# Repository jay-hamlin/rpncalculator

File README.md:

# rpncalculator
RPN Calculator inspired by the HP-97

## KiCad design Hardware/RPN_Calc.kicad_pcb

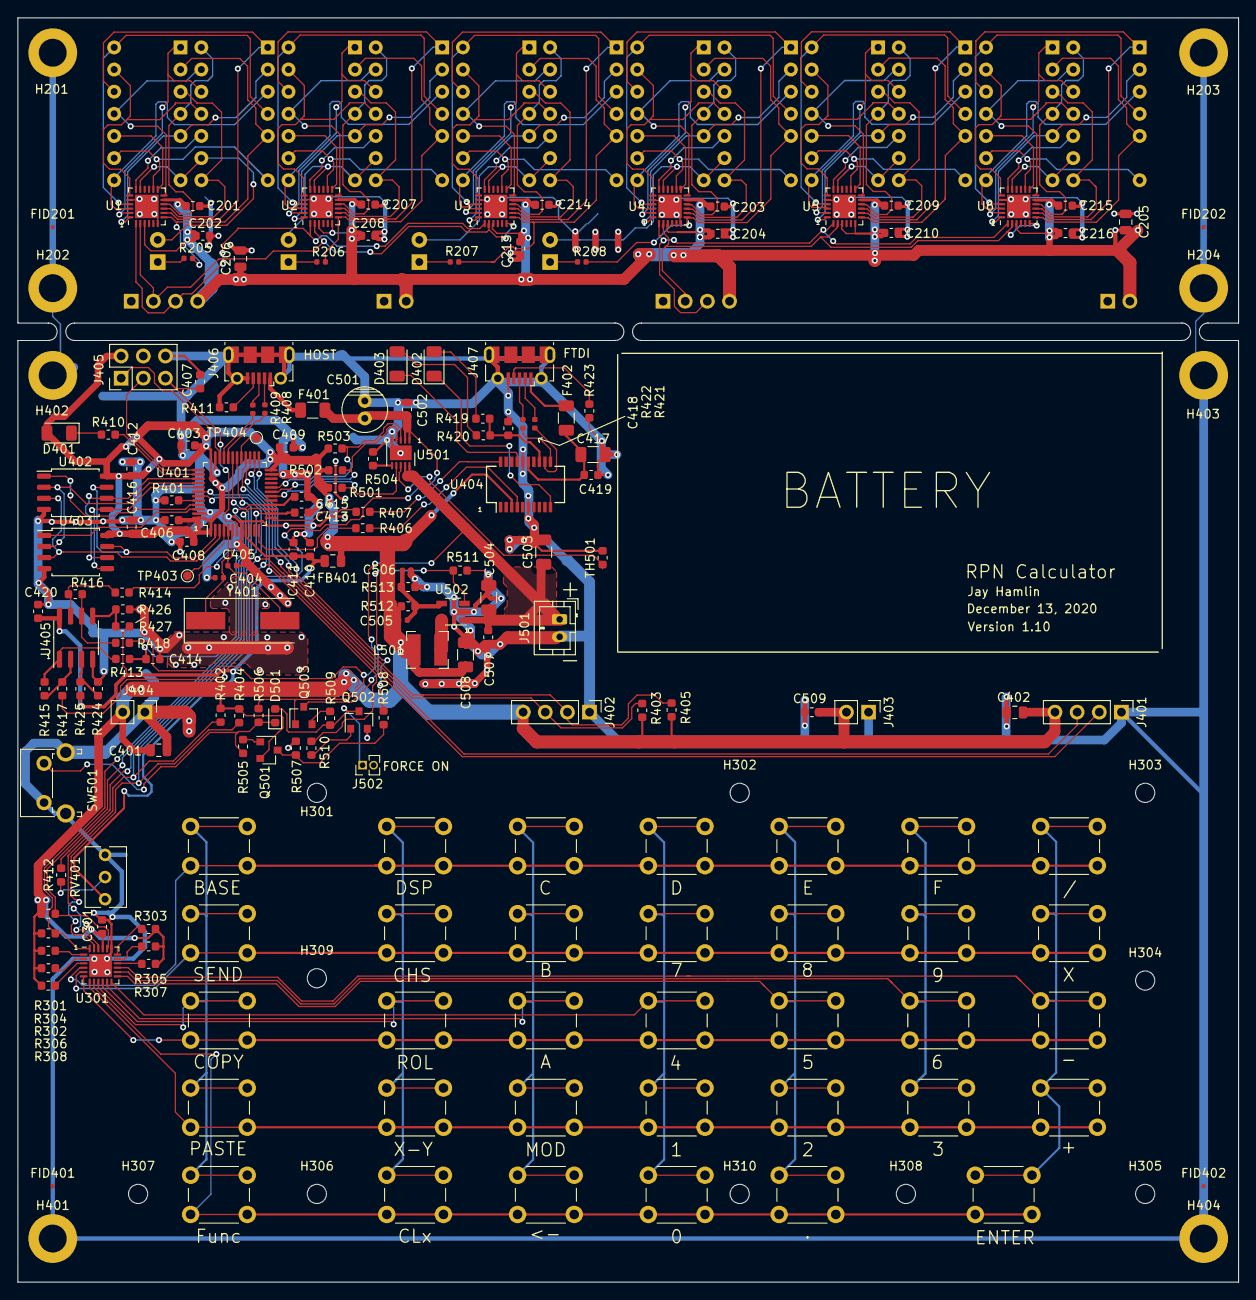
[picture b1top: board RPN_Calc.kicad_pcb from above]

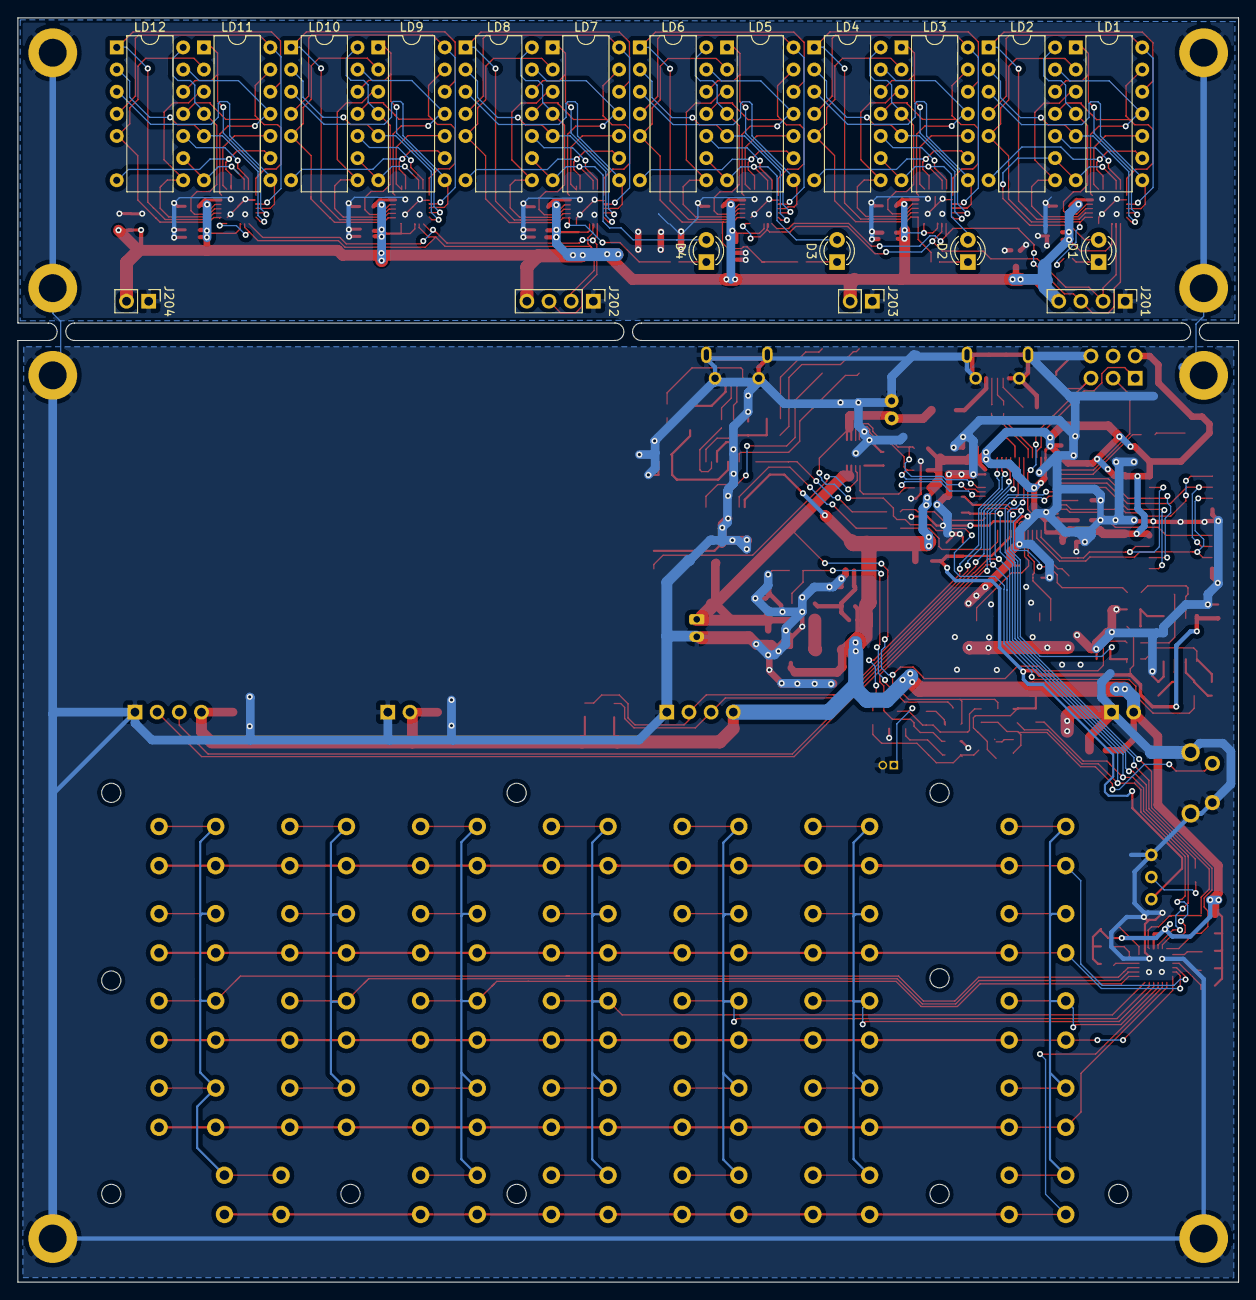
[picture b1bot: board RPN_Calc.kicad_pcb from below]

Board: 2 copper layers, 140.0 x 145.0 mm, 212 parts (20 on the bottom side), 186 nets.

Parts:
0, 1, 2, 3, 4, 5, 6, 7, 8, 9, .: TL1105SPF; SW_PUSH_TL1105
+: TL1105SPF; SW_PUSH_TL1105
-: TL1105SPF; SW_PUSH_TL1105
/: TL1105SPF; SW_PUSH_TL1105
<-: TL1105SPF; SW_PUSH_TL1105
A: TL1105SPF; SW_PUSH_TL1105
B: TL1105SPF; SW_PUSH_TL1105
BASE: TL1105SPF; SW_PUSH_TL1105
C: TL1105SPF; SW_PUSH_TL1105
C201, C203, C207, C209, C213, C215, C301, C403, C406, C407, C408, C409, C410, C412, C413, C414, C415, C416, C418, C419, C420, C507, C509: 100nF; C_0603_1608Metric
C202, C204, C208, C210, C214, C216, C411, C502: 1uF; C_0603_1608Metric
C205, C206, C401, C402: 4.7uF; C_0805_2012Metric
C404, C405: 20pF; C_0402_1005Metric
C417, C503, C504, C508: 10uF; C_1206_3216Metric
C501: 33uF; C_Radial_D5.0mm_H11.0mm_P2.00mm
C505: 7.0pF; C_0402_1005Metric
C506: 33pF; C_0402_1005Metric
CHS: TL1105SPF; SW_PUSH_TL1105
CLx: TL1105SPF; SW_PUSH_TL1105
COPY: TL1105SPF; SW_PUSH_TL1105
D: TL1105SPF; SW_PUSH_TL1105
D1, D2, D3, D4: LED; LED_D3.0mm
D401: LED_GREEN; LED_1206_3216Metric
D402, D403: LED; LED_1206_3216Metric
D501: CDBU0240; D_0603_1608Metric
DSP: TL1105SPF; SW_PUSH_TL1105
E: TL1105SPF; SW_PUSH_TL1105
ENTER: TL1105SPF; SW_PUSH_TL1105
F: TL1105SPF; SW_PUSH_TL1105
F401, F402: Polyfuse_Small; Fuse_1206_3216Metric
FB401: Ferrite_Bead_Small; L_0805_2012Metric
FID201, FID202, FID401, FID402: Fiducial; Fiducial_0.5mm_Mask1mm
Func: TL1105SPF; SW_PUSH_TL1105
H201, H202, H203, H204, H401, H402, H403, H404: MountingHole_Pad; MountingHole_3.2mm_M3_DIN965_Pad
H301, H302, H303, H304, H305, H306, H307, H308, H309, H310: MountingHole; MountingHole_2.2mm_M2
J201, J202, J401, J402: Conn_01x04; PinHeader_1x04_P2.54mm_Vertical
J203, J204, J403, J404: Conn_01x02; PinHeader_1x02_P2.54mm_Vertical
J405: Conn_02x03_Odd_Even; PinHeader_2x03_P2.54mm_Vertical
J406, J407: USB_B_Micro; USB_Micro-B_Molex-105017-0001
J501: JST PTH 2.0mm vertical; JST_PH_B2B-PH-K_1x02_P2.00mm_Vertical
J502: HDR_1x2_50mil; PinHeader_1x02_P1.27mm_Vertical
L501: 2.2uH; L_Bourns-SRN4018
LD1, LD2, LD3, LD4, LD5, LD6, LD7, LD8, LD9, LD10, LD11, LD12: LTP-305HR; DIP-14_LTP-305HR
MOD: TL1105SPF; SW_PUSH_TL1105
PASTE: TL1105SPF; SW_PUSH_TL1105
Q501, Q503: MMBT3906; SOT-23
Q502: 2N7002; SOT-23
R205, R206, R207, R208, R408, R409, R421, R422: 20R; R_0402_1005Metric
R301, R302, R303, R304, R305, R306, R307, R308, R411, R423, R501, R502, R503, R505, R506, R507, R509, R511: 100K; R_0603_1608Metric
R401: 10K; R_0603_1608Metric
R402, R403, R404, R405: 2.2K; R_0603_1608Metric
R406, R407, R412, R413, R414, R419, R420, R508, R510: 1K; R_0603_1608Metric
R410: 240R; R_0603_1608Metric
R415: 549K,1%; R_0603_1608Metric
R416, R418: 2.00M,1%; R_0603_1608Metric
R417: 1.00M,1%; R_0603_1608Metric
R424, R426: 604K,1%; R_0603_1608Metric
R425, R513: 100K,1%; R_0603_1608Metric
R427: 200K,1%; R_0603_1608Metric
R504: 7.8K,1%; R_0603_1608Metric
R512: 500K,1%; R_0603_1608Metric
ROL: TL1105SPF; SW_PUSH_TL1105
RV401: 50K, linear; Potentiometer_Bourns_3266Y_Vertical
SEND: TL1105SPF; SW_PUSH_TL1105
SW501: 1-1825027-1; SW_Tactile_SPST_Angled_PTS645Vx58-2LFS
TH501: 10K, NTC; R_0603_1608Metric
TP403: TEST3; TestPoint_Pad_D1.0mm
TP404: MCO; TestPoint_Pad_D1.0mm
U1, U2, U3, U4, U5, U6: IS31FL3730-QFN24; QFN-24-1EP_4x4mm_P0.5mm_EP2.7x2.7mm
U301: TCA8418RTWR; WQFN-24-1EP_4x4mm_P0.5mm_EP2.6x2.6mm
U401: STM32F070CBTx; LQFP-48_7x7mm_P0.5mm
U402, U403: W25Q128JVS; SOIC-8_5.23x5.23mm_P1.27mm
U404: FT231XS; SSOP-20_3.9x8.7mm_P0.635mm
U405: MCP6422T-E/SN; SOIC-8_3.9x4.9mm_P1.27mm
U501: MCP73833T-FCI_MF; DFN-10-1EP_3x3mm_P0.5mm_EP1.7x2.5mm
U502: LM3671MF; TSOT-23-5
X: TL1105SPF; SW_PUSH_TL1105
X-Y: TL1105SPF; SW_PUSH_TL1105
Y401: 8MHz(12pF); Crystal_SMD_HC49-SD

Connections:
+3V3: C201.1, C202.1, C203.1, C204.1, C205.1, C206.1, C207.1, C208.1, C209.1, C210.1, C213.1, C214.1, C215.1, C216.1, C301.1, C401.1, C402.1, C403.1, C406.1, C408.1, C409.1, C412.1, C416.1, C505.1, C508.1, C509.1, D401.2, FB401.1, J201.4, J202.4, J203.2, J204.2, J401.4, J402.4, J403.2, J404.2, J405.2, L501.2, Q501.2, R301.2, R302.2, R303.1, R304.1, R305.1, R306.1, R307.1, R308.1, R402.2, R403.2, R404.2, R405.2, R501.2, R502.2, R503.2, R512.2, U1.3, U1.11, U2.3, U2.6, U2.11, U3.3, U3.11, U4.3, U4.11, U5.3, U5.6, U5.11, U6.3, U6.11, U301.21, U401.1, U401.24, U401.36, U401.48, U402.8, U403.8, U404.3
/Sheet5F92F4CC/ADC4: C413.1, R412.2, U401.14
/Sheet5F92F4CC/ADC5: C414.1, R413.2, U401.15
/Sheet5F92F4CC/ADC6: C415.1, R414.2, U401.16
/Sheet5F92F4CC/EM1_CS: U401.45, U402.1
/Sheet5F92F4CC/EM2_CS: U401.46, U403.1
/Sheet5F92F4CC/EM_HOLD: U401.2, U402.7, U403.7
/Sheet5F92F4CC/EM_WP: U401.3, U402.3, U403.3
/Sheet5F92F4CC/FT3V3: C418.1, R419.2, R420.2, U404.13
/Sheet5F92F4CC/FT_USBVCC: C417.1, C419.1, F402.1, U404.15
/Sheet5F92F4CC/I2C2_SCL: J402.2, R405.1, U401.26
/Sheet5F92F4CC/I2C2_SDA: J402.3, R403.1, U401.27
/Sheet5F92F4CC/LED1: R410.2, U401.38
/Sheet5F92F4CC/MCU_RX: R407.2, U401.13
/Sheet5F92F4CC/MCU_TX: R406.2, U401.12
/Sheet5F92F4CC/NRST: C407.1, J405.5, U401.7
/Sheet5F92F4CC/OSC_IN: C404.1, U401.5, Y401.1
/Sheet5F92F4CC/OSC_OUT: C405.1, U401.6, Y401.2
/Sheet5F92F4CC/RXD: R406.1, U404.4
/Sheet5F92F4CC/SPI_MISO: U401.40, U402.2, U403.2
/Sheet5F92F4CC/SPI_MOSI: U401.41, U402.5, U403.5
/Sheet5F92F4CC/SPI_SCK: U401.39, U402.6, U403.6
/Sheet5F92F4CC/SWCLK: J405.3, U401.37
/Sheet5F92F4CC/SWDIO: J405.1, U401.34
/Sheet5F92F4CC/TXD: R407.1, U404.20
/Sheet5F92F4CC/USB_DM: R408.2, U401.32
/Sheet5F92F4CC/USB_DP: R409.2, U401.33
/Sheet5F92F4CC/VDDA: C410.1, C411.1, C420.1, FB401.2, R425.1, R427.1, RV401.3, U401.9, U405.8
/Sheet5F92F4CC/VPOT: R412.1, RV401.2
/Sheet5F938EEE/3V3_ENABLE: Q503.3, R511.2, U502.3
/Sheet5F938EEE/THERM: TH501.1, U501.8
/Sheet5FA23E6E/C1A: LD1.5, LD2.2, U1.24
/Sheet5FA23E6E/C1B: LD3.5, LD4.2, U2.24
/Sheet5FA23E6E/C1C: LD5.5, LD6.2, U3.24
/Sheet5FA23E6E/C1D: LD7.5, LD8.2, U4.24
/Sheet5FA23E6E/C1E: LD9.5, LD10.2, U5.24
/Sheet5FA23E6E/C1F: LD11.5, LD12.2, U6.24
/Sheet5FA23E6E/C2A: LD1.1, LD2.12, U1.23
/Sheet5FA23E6E/C2B: LD3.1, LD4.12, U2.23
/Sheet5FA23E6E/C2C: LD5.1, LD6.12, U3.23
/Sheet5FA23E6E/C2D: LD7.1, LD8.12, U4.23
/Sheet5FA23E6E/C2E: LD9.1, LD10.12, U5.23
/Sheet5FA23E6E/C2F: LD11.1, LD12.12, U6.23
/Sheet5FA23E6E/C3A: LD1.8, LD2.3, U1.22
/Sheet5FA23E6E/C3B: LD3.8, LD4.3, U2.22
/Sheet5FA23E6E/C3C: LD5.8, LD6.3, U3.22
/Sheet5FA23E6E/C3D: LD7.8, LD8.3, U4.22
/Sheet5FA23E6E/C3E: LD9.8, LD10.3, U5.22
/Sheet5FA23E6E/C3F: LD11.8, LD12.3, U6.22
/Sheet5FA23E6E/C4A: LD1.14, LD2.4, U1.21
/Sheet5FA23E6E/C4B: LD3.14, LD4.4, U2.21
/Sheet5FA23E6E/C4C: LD5.14, LD6.4, U3.21
/Sheet5FA23E6E/C4D: LD7.14, LD8.4, U4.21
/Sheet5FA23E6E/C4E: LD9.14, LD10.4, U5.21
/Sheet5FA23E6E/C4F: LD11.14, LD12.4, U6.21
/Sheet5FA23E6E/C5A: LD1.13, LD2.11, U1.19
/Sheet5FA23E6E/C5B: LD3.13, LD4.11, U2.19
/Sheet5FA23E6E/C5C: LD5.13, LD6.11, U3.19
/Sheet5FA23E6E/C5D: LD7.13, LD8.11, U4.19
/Sheet5FA23E6E/C5E: LD9.13, LD10.11, U5.19
/Sheet5FA23E6E/C5F: LD11.13, LD12.11, U6.19
/Sheet5FA23E6E/C6A: LD2.10, U1.18
/Sheet5FA23E6E/C6B: LD4.10, U2.18
/Sheet5FA23E6E/C6C: LD6.10, U3.18
/Sheet5FA23E6E/C6D: LD8.10, U4.18
/Sheet5FA23E6E/C6E: LD10.10, U5.18
/Sheet5FA23E6E/C6F: LD12.10, U6.18
/Sheet5FA23E6E/C7A: D1.2, LD1.7, LD2.9, U1.17
/Sheet5FA23E6E/C7B: D2.2, LD3.7, LD4.9, U2.17
/Sheet5FA23E6E/C7C: D3.2, LD5.7, LD6.9, U3.17
/Sheet5FA23E6E/C7D: D4.2, LD7.7, LD8.9, U4.17
/Sheet5FA23E6E/C7E: LD9.7, LD10.9, U5.17
/Sheet5FA23E6E/C7F: LD11.7, LD12.9, U6.17
/Sheet5FA23E6E/R1A: LD1.2, LD2.5, R205.2, U1.7
/Sheet5FA23E6E/R1B: LD3.2, LD4.5, R206.2, U2.7
/Sheet5FA23E6E/R1C: LD5.2, LD6.5, R207.2, U3.7
/Sheet5FA23E6E/R1D: LD7.2, LD8.5, R208.2, U4.7
/Sheet5FA23E6E/R1E: LD9.2, LD10.5, U5.7
/Sheet5FA23E6E/R1F: LD11.2, LD12.5, U6.7
/Sheet5FA23E6E/R2A: LD1.12, LD2.1, U1.8
/Sheet5FA23E6E/R2B: LD3.12, LD4.1, U2.8
/Sheet5FA23E6E/R2C: LD5.12, LD6.1, U3.8
/Sheet5FA23E6E/R2D: LD7.12, LD8.1, U4.8
/Sheet5FA23E6E/R2E: LD9.12, LD10.1, U5.8
/Sheet5FA23E6E/R2F: LD11.12, LD12.1, U6.8
/Sheet5FA23E6E/R3A: LD1.3, LD2.8, U1.9
/Sheet5FA23E6E/R3B: LD3.3, LD4.8, U2.9
/Sheet5FA23E6E/R3C: LD5.3, LD6.8, U3.9
/Sheet5FA23E6E/R3D: LD7.3, LD8.8, U4.9
/Sheet5FA23E6E/R3E: LD9.3, LD10.8, U5.9
/Sheet5FA23E6E/R3F: LD11.3, LD12.8, U6.9
/Sheet5FA23E6E/R4A: LD1.4, LD2.14, U1.10
/Sheet5FA23E6E/R4B: LD3.4, LD4.14, U2.10
/Sheet5FA23E6E/R4C: LD5.4, LD6.14, U3.10
/Sheet5FA23E6E/R4D: LD7.4, LD8.14, U4.10
/Sheet5FA23E6E/R4E: LD9.4, LD10.14, U5.10
/Sheet5FA23E6E/R4F: LD11.4, LD12.14, U6.10
/Sheet5FA23E6E/R5A: LD1.11, LD2.13, U1.12
/Sheet5FA23E6E/R5B: LD3.11, LD4.13, U2.12
/Sheet5FA23E6E/R5C: LD5.11, LD6.13, U3.12
/Sheet5FA23E6E/R5D: LD7.11, LD8.13, U4.12
/Sheet5FA23E6E/R5E: LD9.11, LD10.13, U5.12
/Sheet5FA23E6E/R5F: LD11.11, LD12.13, U6.12
/Sheet5FA23E6E/R6A: LD1.10, U1.13
/Sheet5FA23E6E/R6B: LD3.10, U2.13
/Sheet5FA23E6E/R6C: LD5.10, U3.13
/Sheet5FA23E6E/R6D: LD7.10, U4.13
/Sheet5FA23E6E/R6E: LD9.10, U5.13
/Sheet5FA23E6E/R6F: LD11.10, U6.13
/Sheet5FA23E6E/R7A: LD1.9, LD2.7, U1.14
/Sheet5FA23E6E/R7B: LD3.9, LD4.7, U2.14
/Sheet5FA23E6E/R7C: LD5.9, LD6.7, U3.14
/Sheet5FA23E6E/R7D: LD7.9, LD8.7, U4.14
/Sheet5FA23E6E/R7E: LD9.9, LD10.7, U5.14
/Sheet5FA23E6E/R7F: LD11.9, LD12.7, U6.14
/Sheet5FA23F01/SWROW0: 0.1, 0.2, ..1, ..2, <-.1, <-.2, CLx.1, CLx.2, ENTER.1, ENTER.2, Func.1, Func.2, U301.8
/Sheet5FA23F01/SW_COL0: BASE.3, BASE.4, COPY.3, COPY.4, Func.3, Func.4, PASTE.3, PASTE.4, SEND.3, SEND.4, U301.9
/Sheet5FA23F01/SW_COL1: CHS.3, CHS.4, CLx.3, CLx.4, DSP.3, DSP.4, ROL.3, ROL.4, U301.10, X-Y.3, X-Y.4
/Sheet5FA23F01/SW_COL2: <-.3, <-.4, A.3, A.4, B.3, B.4, C.3, C.4, MOD.3, MOD.4, U301.11
/Sheet5FA23F01/SW_COL3: 0.3, 0.4, 1.3, 1.4, 4.3, 4.4, 7.3, 7.4, D.3, D.4, U301.12
/Sheet5FA23F01/SW_COL4: 2.3, 2.4, 5.3, 5.4, 8.3, 8.4, ..3, ..4, E.3, E.4, U301.13
/Sheet5FA23F01/SW_COL5: 3.3, 3.4, 6.3, 6.4, 9.3, 9.4, F.3, F.4, U301.14
/Sheet5FA23F01/SW_COL6: +.3, +.4, -.3, -.4, /.3, /.4, ENTER.3, ENTER.4, U301.15, X.3, X.4
/Sheet5FA23F01/SW_ROW1: 1.1, 1.2, 2.1, 2.2, 3.1, 3.2, +.1, +.2, MOD.1, MOD.2, PASTE.1, PASTE.2, U301.7, X-Y.1, X-Y.2
/Sheet5FA23F01/SW_ROW2: 4.1, 4.2, 5.1, 5.2, 6.1, 6.2, -.1, -.2, A.1, A.2, COPY.1, COPY.2, ROL.1, ROL.2, U301.6
/Sheet5FA23F01/SW_ROW3: 7.1, 7.2, 8.1, 8.2, 9.1, 9.2, B.1, B.2, CHS.1, CHS.2, SEND.1, SEND.2, U301.5, X.1, X.2
/Sheet5FA23F01/SW_ROW4: /.1, /.2, BASE.1, BASE.2, C.1, C.2, D.1, D.2, DSP.1, DSP.2, E.1, E.2, F.1, F.2, U301.4
BATT_PG: R501.1, U401.18, U501.7
BATT_STAT1: R503.1, U401.20, U501.3
BATT_STAT2: R502.1, U401.19, U501.4
BUTTON_DN: R508.2, U401.25
GND: C201.2, C202.2, C203.2, C204.2, C205.2, C206.2, C207.2, C208.2, C209.2, C210.2, C213.2, C214.2, C215.2, C216.2, C301.2, C401.2, C402.2, C403.2, C404.2, C405.2, C406.2, C407.2, C408.2, C409.2, C410.2, C411.2, C412.2, C413.2, C414.2, C415.2, C416.2, C417.2, C418.2, C419.2, C420.2, C501.2, C502.2, C503.2, C504.2, C506.2, C507.2, C508.2, C509.2, H201.1, H202.1, H203.1, H204.1, H401.1, H402.1, H403.1, H404.1, J201.1, J202.1, J203.1, J204.1, J401.1, J402.1, J403.1, J404.1, J405.6, J406.5, J406.6, J407.5, J407.6, J501.2, J502.2, Q502.2, R401.2, R411.2, R423.2, R424.2, R426.2, R504.1, R507.1, R511.1, R513.1, RV401.1, SW501.1, SW501.3, SW501.4, TH501.2, U1.6, U1.20, U1.25, U2.20, U2.25, U3.20, U3.25, U4.6, U4.20, U4.25, U5.20, U5.25, U6.20, U6.25, U301.19, U301.25, U401.8, U401.23, U401.35, U401.47, U402.4, U403.4, U404.6, U404.16, U405.4, U501.5, U501.11, U502.2
I2C1_SCL: J401.2, R404.1, U301.23, U401.42
I2C1_SDA: J401.3, R402.1, U301.22, U401.43
I2C_SCL_A: J201.2, U1.2, U2.2, U3.2, U3.6
I2C_SCL_B: J202.2, U4.2, U5.2, U6.2, U6.6
I2C_SDA_A: J201.3, U1.1, U2.1, U3.1
I2C_SDA_B: J202.3, U4.1, U5.1, U6.1
KEYBD_INT: R302.1, U301.24, U401.31
KEYBD_RST: R301.1, U301.20, U401.30
unnamed: C505.2, C506.1, R512.1, R513.2, U502.4
unnamed: D1.1, R205.1
unnamed: D2.1, R206.1
unnamed: D3.1, R207.1
unnamed: D4.1, R208.1
unnamed: D401.1, R410.1
unnamed: D402.1, U404.10
unnamed: D402.2, R419.1
unnamed: D403.1, U404.17
unnamed: D403.2, R420.1
unnamed: D501.1, R505.2, R506.1, SW501.2
unnamed: D501.2, J502.1, Q502.3, R509.2
unnamed: F401.2, J406.1
unnamed: F402.2, J407.1
unnamed: J406.2, R408.1
unnamed: J406.3, R409.1
unnamed: J406.4, R411.1
unnamed: J407.2, R421.1
unnamed: J407.3, R422.1
unnamed: J407.4, R423.1
unnamed: L501.1, U502.5
unnamed: Q501.1, R505.1
unnamed: Q501.3, R507.2, R508.1
unnamed: Q502.1, R510.1
unnamed: Q503.2, R509.1
unnamed: R303.2, U301.18
unnamed: R304.2, U301.1
unnamed: R305.2, U301.17
unnamed: R306.2, U301.2
unnamed: R307.2, U301.16
unnamed: R308.2, U301.3
unnamed: R401.1, U401.44
unnamed: R413.1, R415.2, U405.1
unnamed: R414.1, R416.2, U405.7
unnamed: R415.1, R417.2, U405.2
unnamed: R416.1, R418.2, U405.6
unnamed: R421.2, U404.12
unnamed: R422.2, U404.11
unnamed: R424.1, R425.2, U405.3
unnamed: R426.1, R427.2, U405.5
unnamed: R504.2, U501.6
unnamed: TP403.1, U401.4
unnamed: TP404.1, U401.29
PWR_HOLD: R510.2, U401.28
USBVBUS: C501.1, C502.1, F401.1, R417.1, U501.1, U501.2
VBATT_RAW: C503.1, C504.1, C507.1, J501.1, Q503.1, R418.1, R506.2, U501.9, U501.10, U502.1

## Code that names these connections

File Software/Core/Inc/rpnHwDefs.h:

/*
 * rpnHwDefs.h
 *
 *  Created on: Dec 3, 2020
 *      Author: jayhamlin
 */

#ifndef INC_RPNHWDEFS_H_
#define INC_RPNHWDEFS_H_

// signals to the MCU
// PORT A
#define	NC_PA0			GPIO_PIN_0
#define	NC_PA1			GPIO_PIN_1
#define	PIN_UART_TX		GPIO_PIN_2
#define	PIN_UART_RX		GPIO_PIN_3
#define	PIN_ADC4_POT	GPIO_PIN_4
#define	PIN_ADC5_USB	GPIO_PIN_5
#define	PIN_ADC6_BAT	GPIO_PIN_6
#define	NC_PA7			GPIO_PIN_7
#define	PIN_TP404		GPIO_PIN_8
#define	PIN_KEYBD_RST	GPIO_PIN_9
#define	PIN_KEYBD_INT	GPIO_PIN_10
#define	PIN_USB_DM		GPIO_PIN_11
#define	PIN_USB_DP		GPIO_PIN_12
#define	PIN_SWDIO		GPIO_PIN_13
#define	PIN_SWCLK		GPIO_PIN_14
#define	PIN_LED1		GPIO_PIN_15
// PORT B
#define	PIN_CHGR_PG		GPIO_PIN_0
#define	PIN_CHGR_STAT2	GPIO_PIN_1
#define	PIN_CHGR_STAT1	GPIO_PIN_2
#define	PIN_SPI_SCLK	GPIO_PIN_3
#define	PIN_SPI_MISO	GPIO_PIN_4
#define	PIN_SPI_MOSI	GPIO_PIN_5
#define	PIN_I2C1_SCL	GPIO_PIN_6
#define	PIN_I2C1_SDA	GPIO_PIN_7
#define	PIN_EM1_CS		GPIO_PIN_8
#define	PIN_EM2_CS		GPIO_PIN_9
#define	NC_PB10			GPIO_PIN_10
#define	NC_PB11			GPIO_PIN_11
#define	PIN_BUTTON_DN	GPIO_PIN_12
#define	PIN_I2C2_SCL	GPIO_PIN_13
#define	PIN_I2C2_SDA	GPIO_PIN_14
#define	PIN_PWR_HOLD	GPIO_PIN_15

// some useful macros
#define POWER_SUPPLY_HOLD(a) 	HAL_GPIO_WritePin(GPIOB,PIN_PWR_HOLD,a)
#define KEYPAD_RESET(a)			HAL_GPIO_WritePin(GPIOA,PIN_KEYBD_RST,(a^1))  // bit flip to make positive true
#define LED(a) 					HAL_GPIO_WritePin(GPIOA,GPIO_PIN_15, (a^1)) // bit flip to make positive true

#define READ_PUSHBUTTON()		HAL_GPIO_ReadPin(GPIOB, PIN_BUTTON_DN) // button is positive true
#define READ_CHARGER_STATUS(a)	HAL_GPIO_ReadPin(GPIOB, a) // PIN_CHGR_PG,PIN_CHGR_STAT1,PIN_CHGR_STAT2

// ADC channels -
//		The values in adcValues are updated once per second
#define		ADC_CHANNEL_COUNT		5
#define		ADC_INDEX_POT			0
#define		ADC_INDEX_USB			1
#define		ADC_INDEX_BATT			2
#define		ADC_INDEX_TEMP			3
#define		ADC_INDEX_VREF			4



#endif /* INC_RPNHWDEFS_H_ */

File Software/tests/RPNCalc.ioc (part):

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Mcu.Name=STM32F070CBTx
Mcu.Package=LQFP48
Mcu.UserName=STM32F070CBTx
PA10.Signal=GPXTI10
PA11.Mode=Device
PA11.Signal=USB_DM
PA12.Mode=Device
PA12.Signal=USB_DP
PA15.Signal=GPIO_Output
PA2.Mode=Asynchronous
PA2.Signal=USART2_TX
PA3.Mode=Asynchronous
PA3.Signal=USART2_RX
PA4.Mode=IN4
PA4.Signal=ADC_IN4
PA5.Mode=IN5
PA5.Signal=ADC_IN5
PA6.Mode=IN6
PA6.Signal=ADC_IN6
PA8.Mode=Clock-out
PA8.Signal=RCC_MCO
PA9.Signal=GPIO_Output
PB0.Signal=GPIO_Input
PB1.Signal=GPIO_Input
PB12.Signal=GPIO_Input
PB13.Mode=I2C
PB13.Signal=I2C2_SCL
PB14.Mode=I2C
PB14.Signal=I2C2_SDA
PB15.Signal=GPIO_Output
PB2.Signal=GPIO_Input
PB3.Signal=SPI1_SCK
PB4.Signal=SPI1_MISO
PB5.Signal=SPI1_MOSI
PB6.Mode=I2C
PB6.Signal=I2C1_SCL
PB7.Mode=I2C
PB7.Signal=I2C1_SDA
PB8.Signal=GPIO_Output
PB9.Signal=GPIO_Output
PC13.Signal=GPIO_Output
PC14-OSC32_IN.Signal=GPIO_Output
PC15-OSC32_OUT.Signal=GPIO_Output
PF0-OSC_IN.Mode=HSE-External-Oscillator
PF0-OSC_IN.Signal=RCC_OSC_IN
PF1-OSC_OUT.Mode=HSE-External-Oscillator
PF1-OSC_OUT.Signal=RCC_OSC_OUT
RCC.SYSCLKFreq_VALUE=48000000
RCC.SYSCLKSource=RCC_SYSCLKSOURCE_PLLCLK
board=custom

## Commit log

2020-12-23 First checkin Hardware
2020-12-23 First checkin Software
2020-12-26 added some test cases from python.
2020-12-29 working pretty well now. new MCU
2020-12-29 adding STM32CubeIDE project file
2021-01-01 Adding latest keyboard design
2021-01-01 fix bug in divide. result exp to int16_t
2021-01-01 fixed stack manipulation
2021-01-03 more stack fixes, NAN in divide works,Modulo
